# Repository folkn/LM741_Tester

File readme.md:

# LM741 Op-Amp Tester

A design for a homemade one-sided PCB LM741 Op-Amp Tester.

## Components

All are through-hole THT components.

Diode (1N4007)   x 2

Resistors

  4.7K   x 1

  1.0K   x 1

  10.K   x 3

Capacitor (10 uF) x 1

LM741 or 8-pin socket x 1

LED x 1

9V Power Supply or 9V Battery Holder  x 1

## Usage

If the LM741 is working, the LED will blink.

If the LM741 is not working, the LED will stay on or off and not blink.

This circuit works by setting up an oscillator circuit which causes the 
LED to flicker.

A 9V supply is required, either through the pins (9V battery connector) or 
through the pads (alligator clips)

## Files and Fabrication

The source file can be opened in KiCad 6.0 and edited as you wish.

A CNC/PCB mill or an etching process can be used as the design is 
single-sided. If  you're feeling like it, copper tape or conductive ink 
works too! 

I designed this PCB for a laboratory course I am teaching.
This code is released under the CC-BY-3.0 license.

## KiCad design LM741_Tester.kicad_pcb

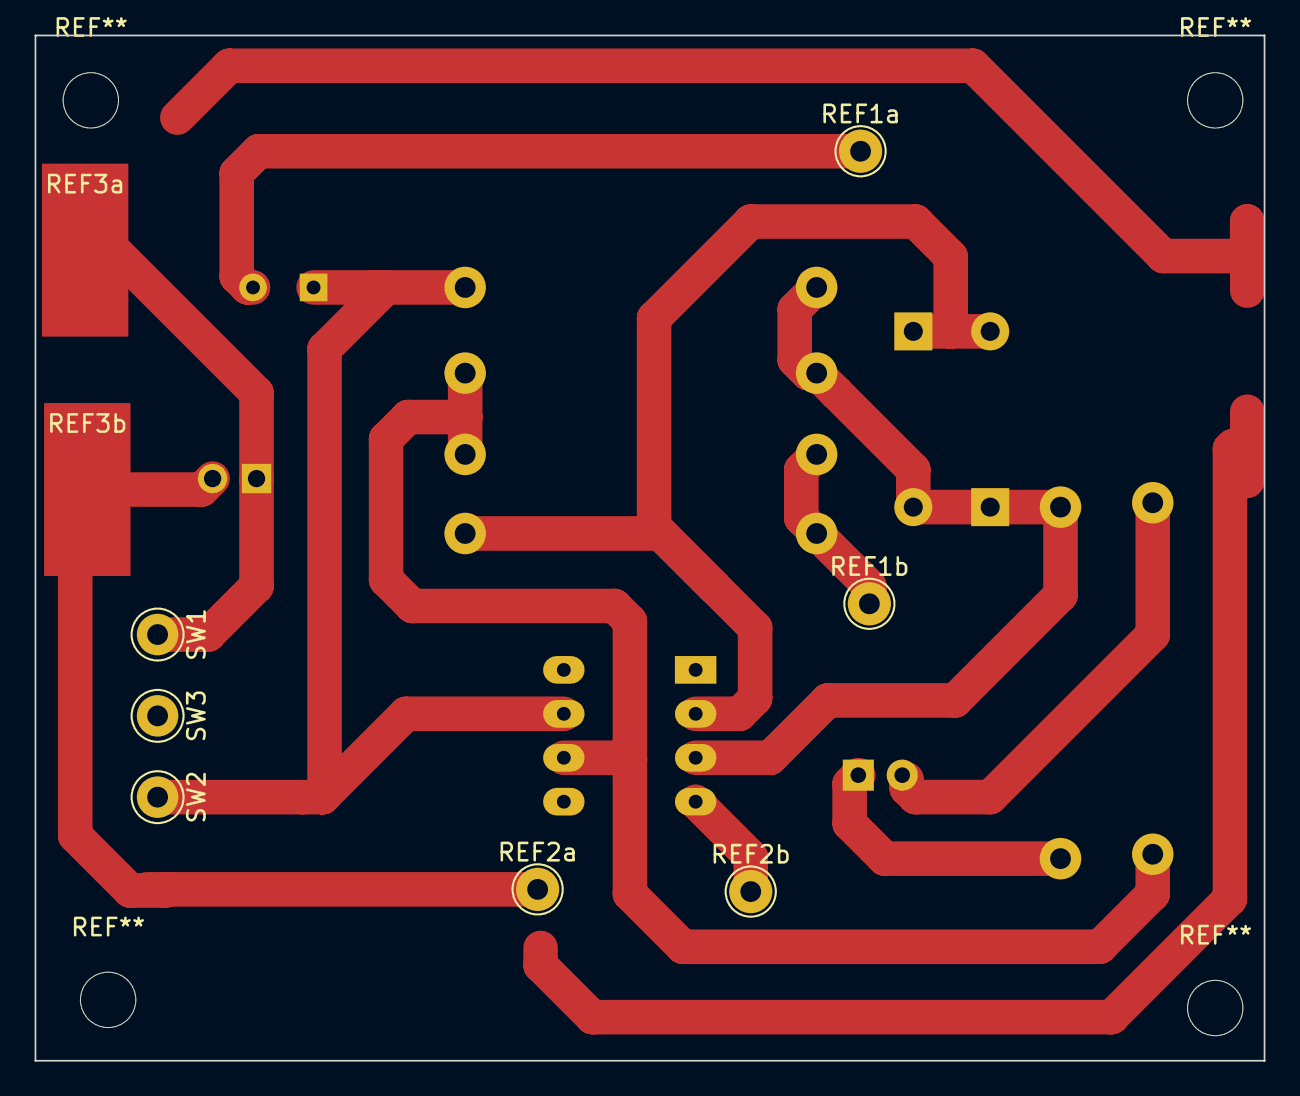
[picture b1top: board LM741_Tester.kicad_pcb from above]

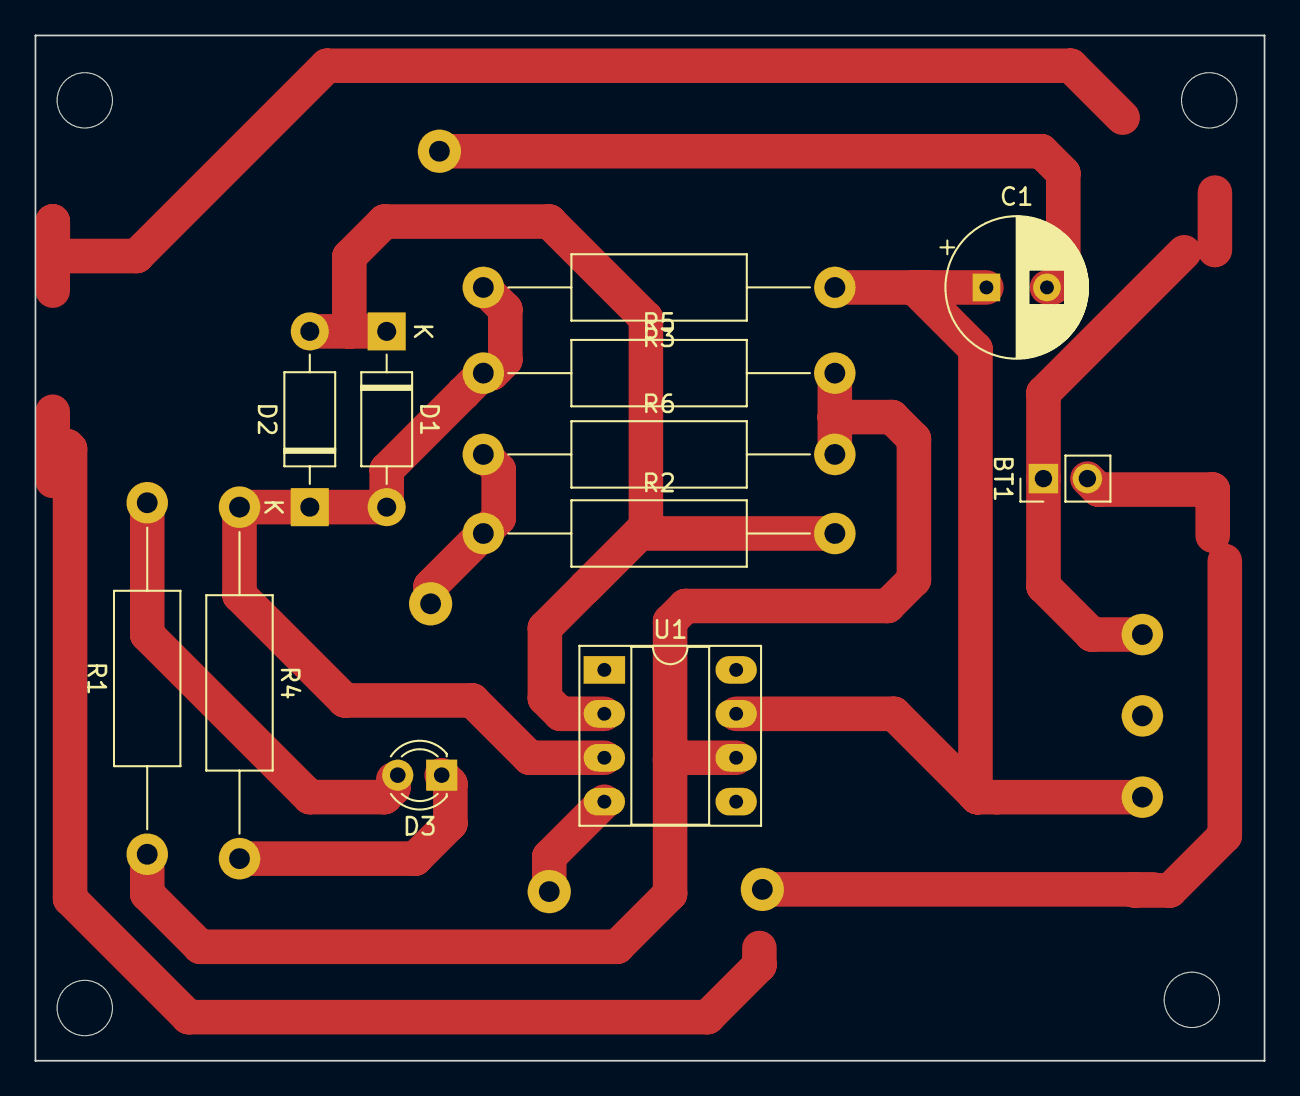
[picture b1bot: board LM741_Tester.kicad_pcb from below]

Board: 2 copper layers, 71.1 x 59.3 mm, 21 parts (12 on the bottom side), 9 nets.

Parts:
BT1: Battery_Cell; PinHeader_1x02_P2.54mm_Vertical
C1: C; CP_Radial_D8.0mm_P3.50mm
D1, D2: 1N4007; D_DO-41_SOD81_P10.16mm_Horizontal
D3: LED; LED_D3.0mm
R1: 1k; R_Axial_DIN0411_L9.9mm_D3.6mm_P20.32mm_Horizontal
R2, R3, R4, R6: 10k; R_Axial_DIN0411_L9.9mm_D3.6mm_P20.32mm_Horizontal
R5: 4.7k; R_Axial_DIN0411_L9.9mm_D3.6mm_P20.32mm_Horizontal
REF1a, REF1b, REF2a, REF2b: TestPoint_THTPad_D2.5mm_Drill1.2mm
REF3a, REF3b: SolderWirePad_1x01_SMD_5x10mm
SW1, SW2, SW3: Switch; Pin_D1.0mm_L10.0mm_LooseFit
U1: LM741; DIP-8_W7.62mm_Socket_LongPads

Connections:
GND: BT1.2 (-), REF2a.1, REF2b.1, REF3b.1, U1.4 (V-)
unnamed: R1.1, R5.2, R6.2, U1.6
unnamed: D3.2 (A), R1.2
unnamed: C1.2, R2.1, R6.1, REF1a.1, REF1b.1
unnamed: D1.1 (K), D2.2 (A), R2.2, U1.2 (-)
unnamed: D1.2 (A), D2.1 (K), R3.2, R4.1, R5.1, U1.3 (+)
unnamed: D3.1 (K), R4.2
unnamed: BT1.1 (+), REF3a.1, SW1.1
unnamed: C1.1, R3.1, SW2.1, U1.7 (V+)
